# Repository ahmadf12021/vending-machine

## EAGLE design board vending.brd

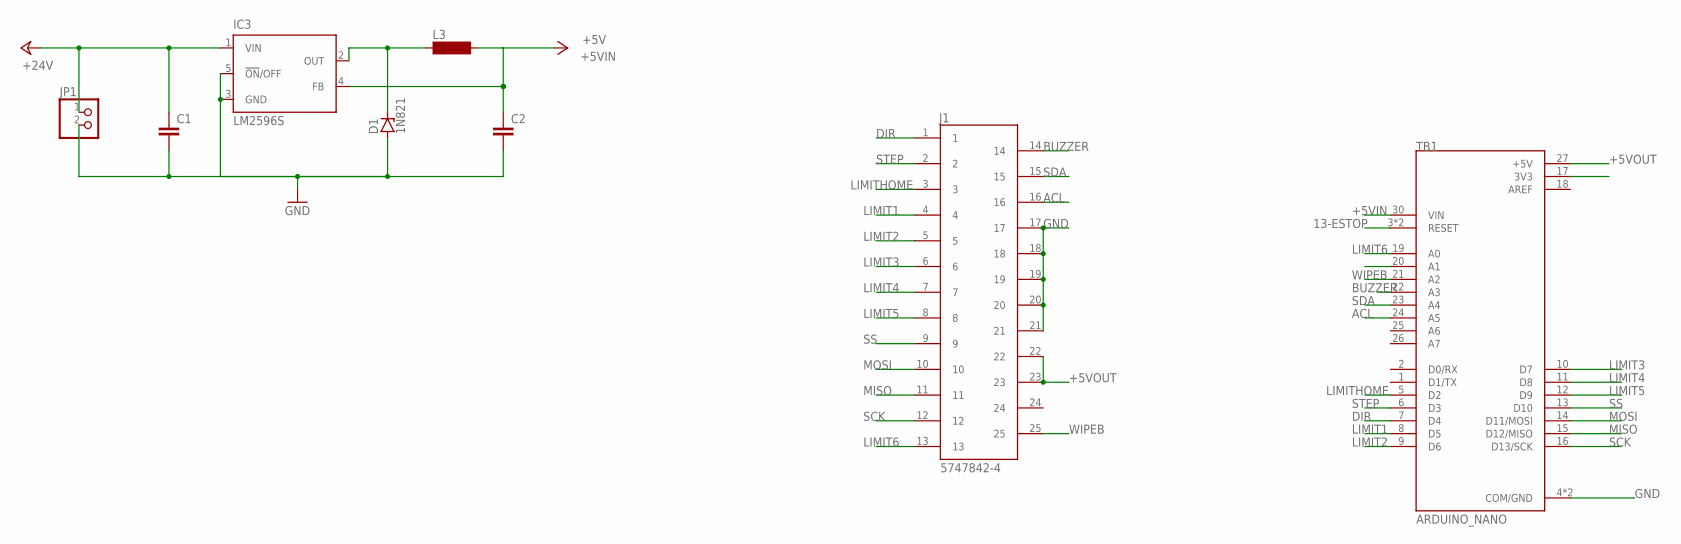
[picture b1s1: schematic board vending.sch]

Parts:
C1, C2: C5/7.2; C5B7.2
D1: 1N821; DO35Z10
IC3: LM2596S; TO263-5
J1: 5747842-4; TE_5747842-4
JP1: PINHD-1X2; 1X02
L3: BS75
TB1: ARDUINO_NANO; SHIELD_ARDUINO_NANO

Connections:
13-ESTOP: TB1.3 (RESET), TB1.28 (RESET)
+5VIN: C2.1, IC3.4 (FB), L3.2, TB1.30 (VIN)
+5VOUT: J1.22, J1.23, TB1.27 (+5V)
+24V: C1.1, IC3.1 (VIN), JP1.1
ACL: J1.16, TB1.24 (A5)
AREF: TB1.18 (AREF)
BUZZER: J1.14, TB1.22 (A3)
DIR: J1.1, TB1.7 (D4)
GND: C1.2, C2.2, D1.A, IC3.3 (GND), IC3.5 (!ON!/OFF), J1.17, J1.18, J1.19, J1.20, J1.21, JP1.2, TB1.4 (COM/GND), TB1.29 (COM/GND)
LIMIT1: J1.4, TB1.8 (D5)
LIMIT2: J1.5, TB1.9 (D6)
LIMIT3: J1.6, TB1.10 (D7)
LIMIT4: J1.7, TB1.11 (D8)
LIMIT5: J1.8, TB1.12 (D9)
LIMIT6: J1.13, TB1.19 (A0)
LIMITHOME: J1.3, TB1.5 (D2)
MISO: J1.11, TB1.15 (D12/MISO)
MOSI: J1.10, TB1.14 (D11/MOSI)
unnamed: D1.C, IC3.2 (OUT), L3.1
SCK: J1.12, TB1.16 (D13/SCK)
SDA: J1.15, TB1.23 (A4)
SS: J1.9, TB1.13 (D10)
STEP: J1.2, TB1.6 (D3)
WIPEB: J1.25, TB1.21 (A2)

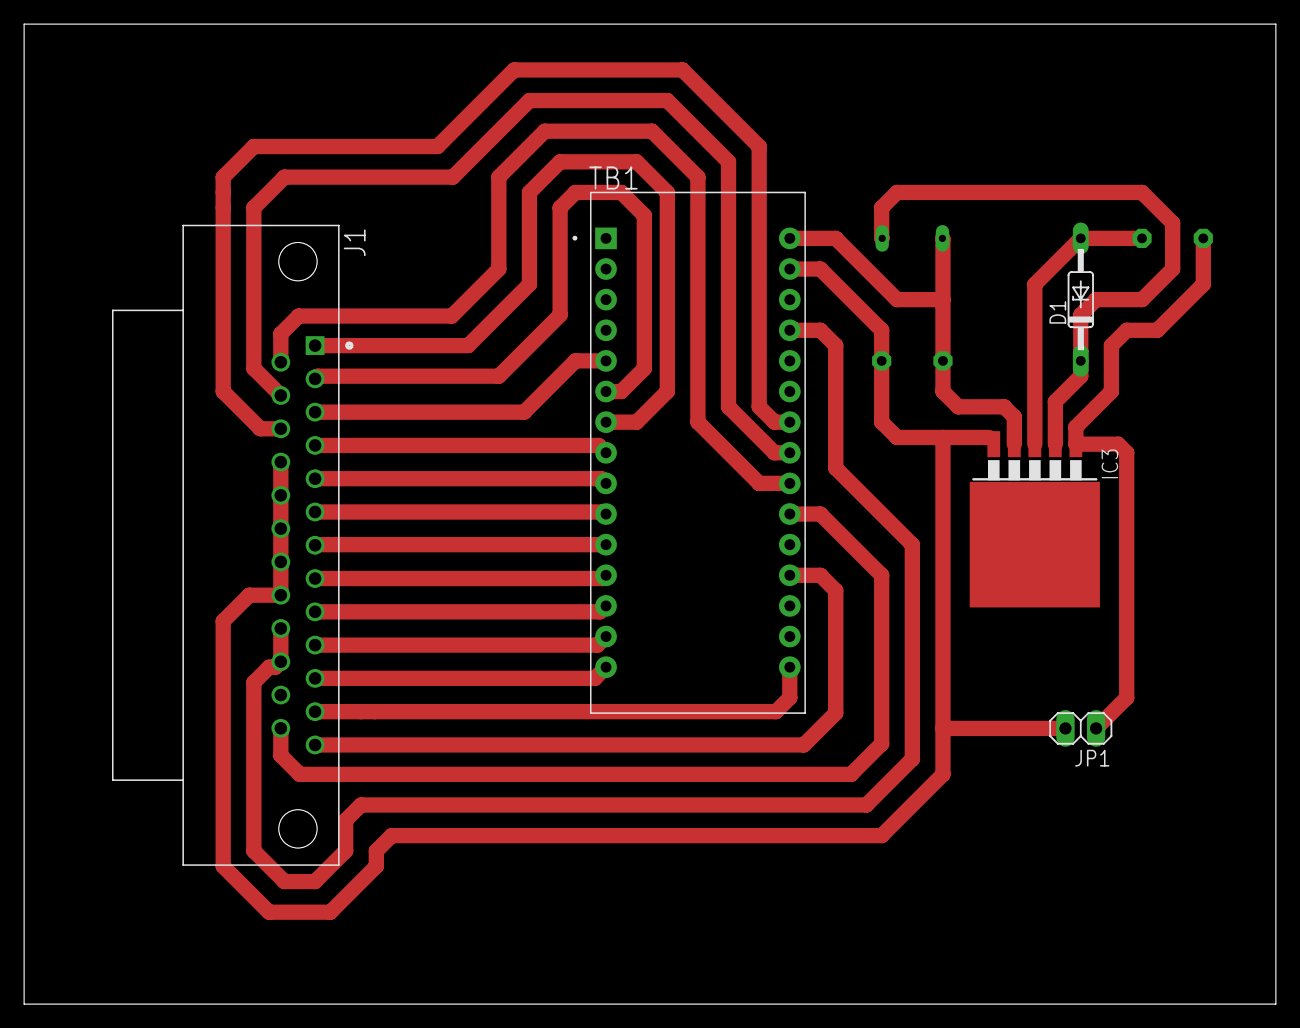
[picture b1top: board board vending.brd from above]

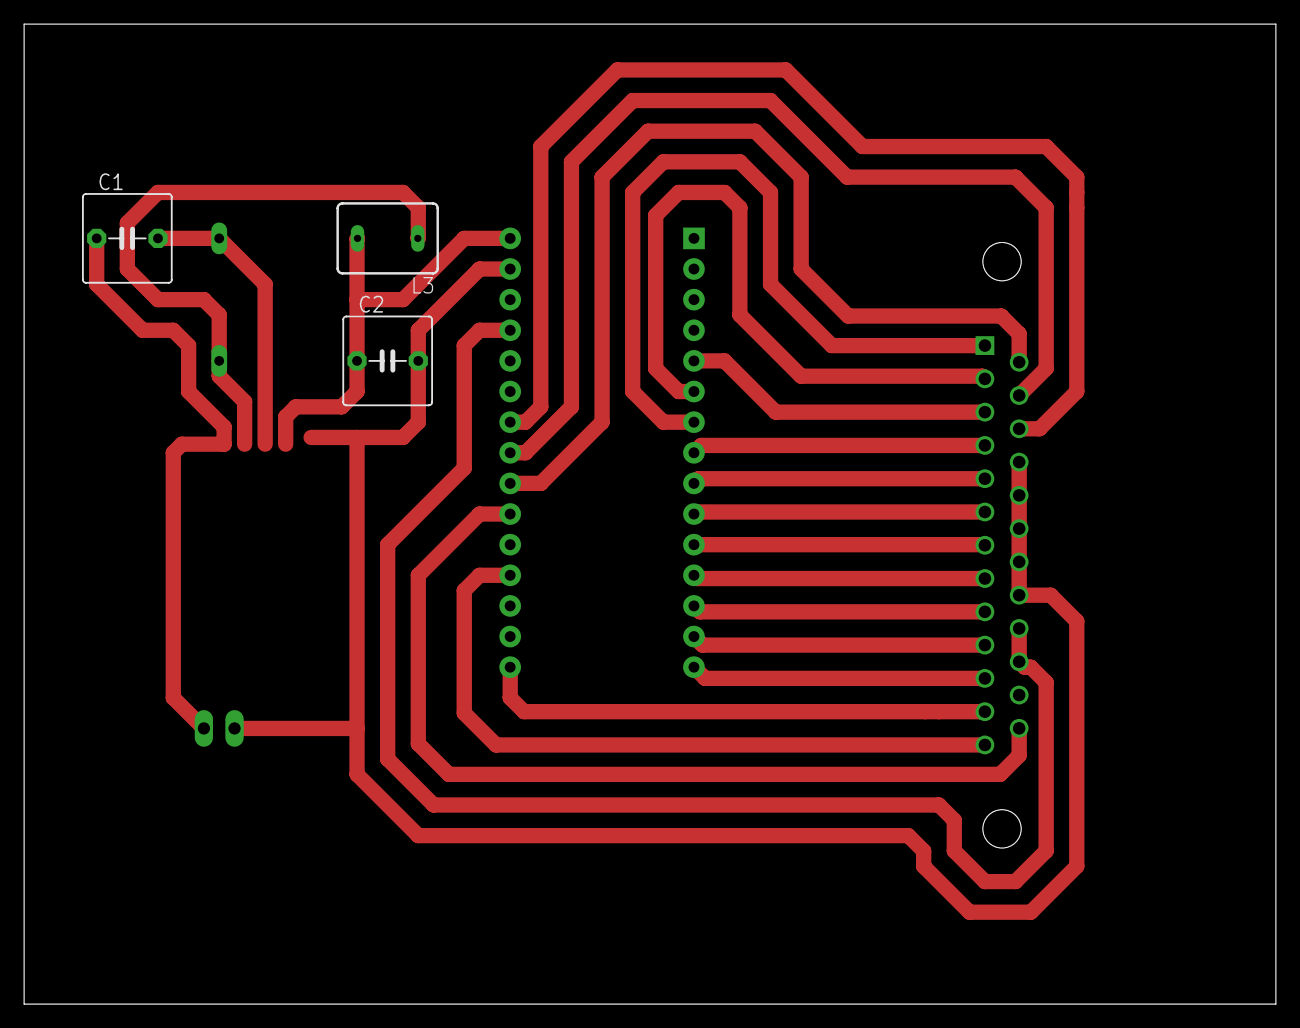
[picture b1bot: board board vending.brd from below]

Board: 2 copper layers, 103.8 x 81.3 mm, 8 parts (3 on the bottom side), 23 nets.

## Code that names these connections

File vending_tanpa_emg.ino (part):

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#define LED_ON HIGH
#define LED_OFF LOW
#endif
#define buzzer A3
#define wipeB A2 // Button pin for WipeMode
//------------------------------------------------------------------------------
#define limit1 5
#define limit2 6
#define limit3 7
#define limit4 8
#define limit5 9
#define limit6 A0
#define tapcard A1
#define dirPin 4
#define stepPin 3
#define limithome 2
#define emergency A7
#define stepsPerRevolution 3600
//--------------------------------------------------------------------------------
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
 pinMode(stepPin, OUTPUT);
  pinMode(dirPin, OUTPUT);
  pinMode(limit1, INPUT_PULLUP); //box 1 ada di pin 4 arduino begitupun seterusnya untuk box yang lain
  pinMode(limit2, INPUT_PULLUP);
  pinMode(limit3, INPUT_PULLUP);
  pinMode(limit4, INPUT_PULLUP);
  pinMode(limit5, INPUT_PULLUP);
  pinMode(limit6, INPUT_PULLUP);
  pinMode(limithome,INPUT_PULLUP);
  pinMode(tapcard,INPUT_PULLUP);
  pinMode(emergency,INPUT_PULLUP);
  pinMode(13,1);
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      delay(1000);
  //-----------------------------------------------------------------------
  //Arduino Pin Configuration
  pinMode(buzzer, OUTPUT);
  pinMode(wipeB, INPUT_PULLUP);   // Enable pin's pull up resistor
  digitalWrite(buzzer, LED_OFF); // Make sure led is off
  //Protocol Configuration
  Serial.begin(9600);  // Initialize serial communications with PC
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  ShowReaderDetails();  // Show details of PCD - MFRC522 Card Reader details

  //Wipe Code - If the Button (wipeB) Pressed while setup run (powered on) it wipes EEPROM
  if (digitalRead(wipeB) == LOW) {  // when button pressed pin should get low, button connected to ground
    Serial.println(F("Wipe Button Pressed"));
    Serial.println(F("You have 15 seconds to Cancel"));
    Serial.println(F("This will be remove all records and cannot be undone"));
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  Serial.println(F("Waiting PICCs to be scanned"));
  cycleLeds();    // Everything ready lets give user some feedback by cycling leds
//----------------------------------------------------------------------
attachInterrupt(digitalPinToInterrupt(limithome), trigg, CHANGE);

while (homing == 1)
  {
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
